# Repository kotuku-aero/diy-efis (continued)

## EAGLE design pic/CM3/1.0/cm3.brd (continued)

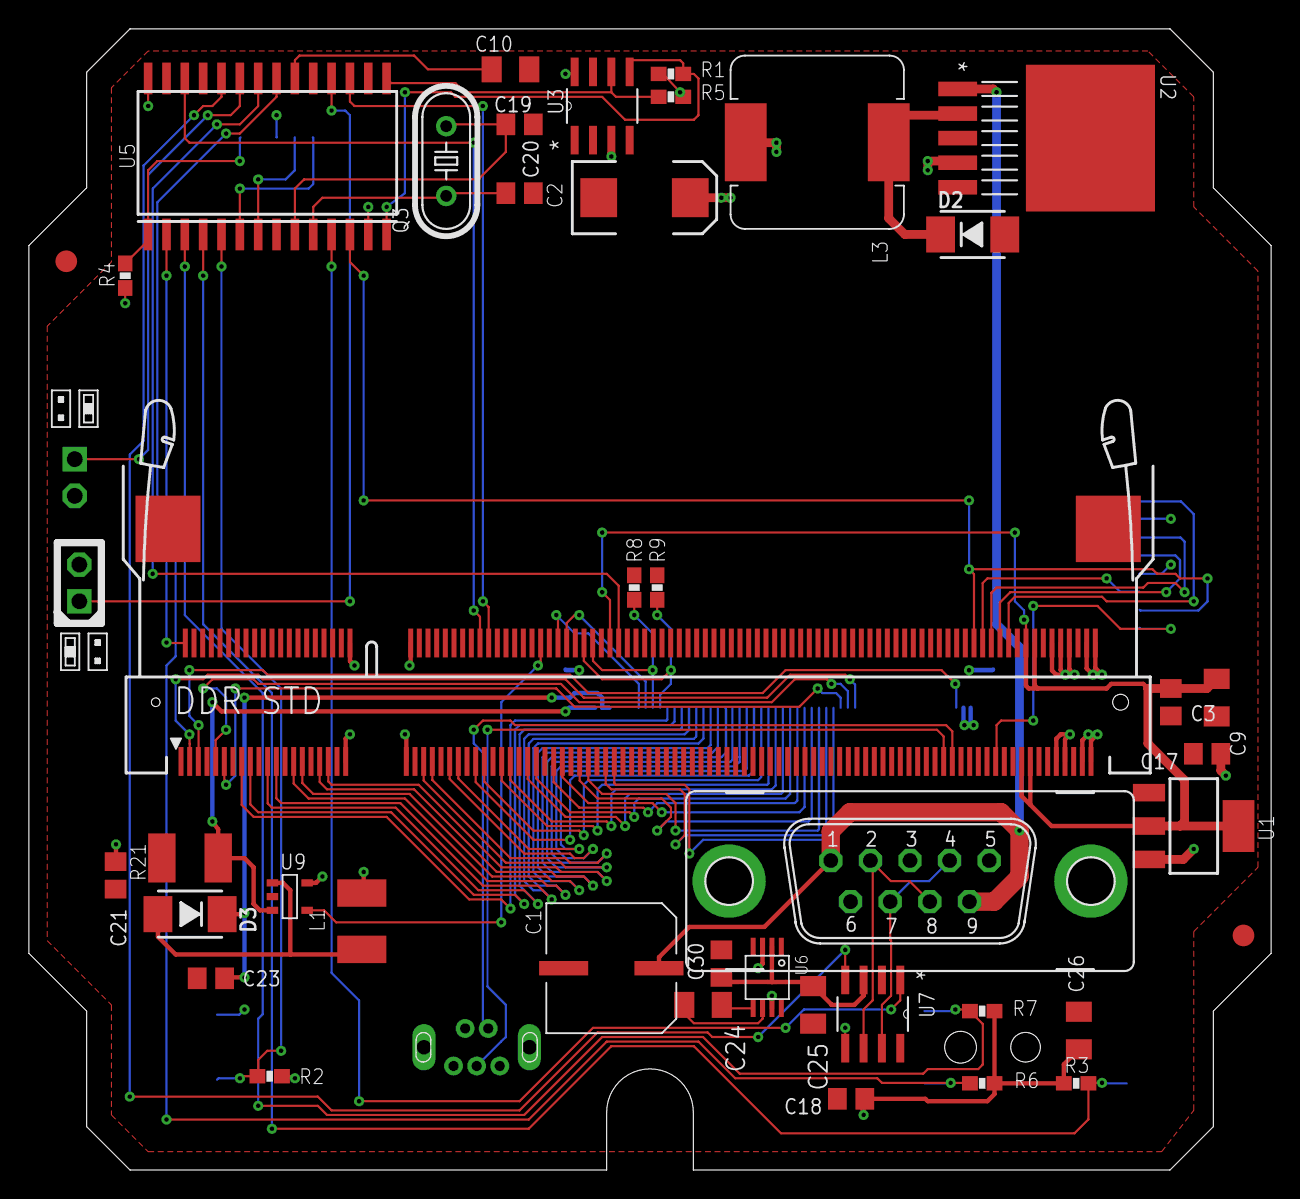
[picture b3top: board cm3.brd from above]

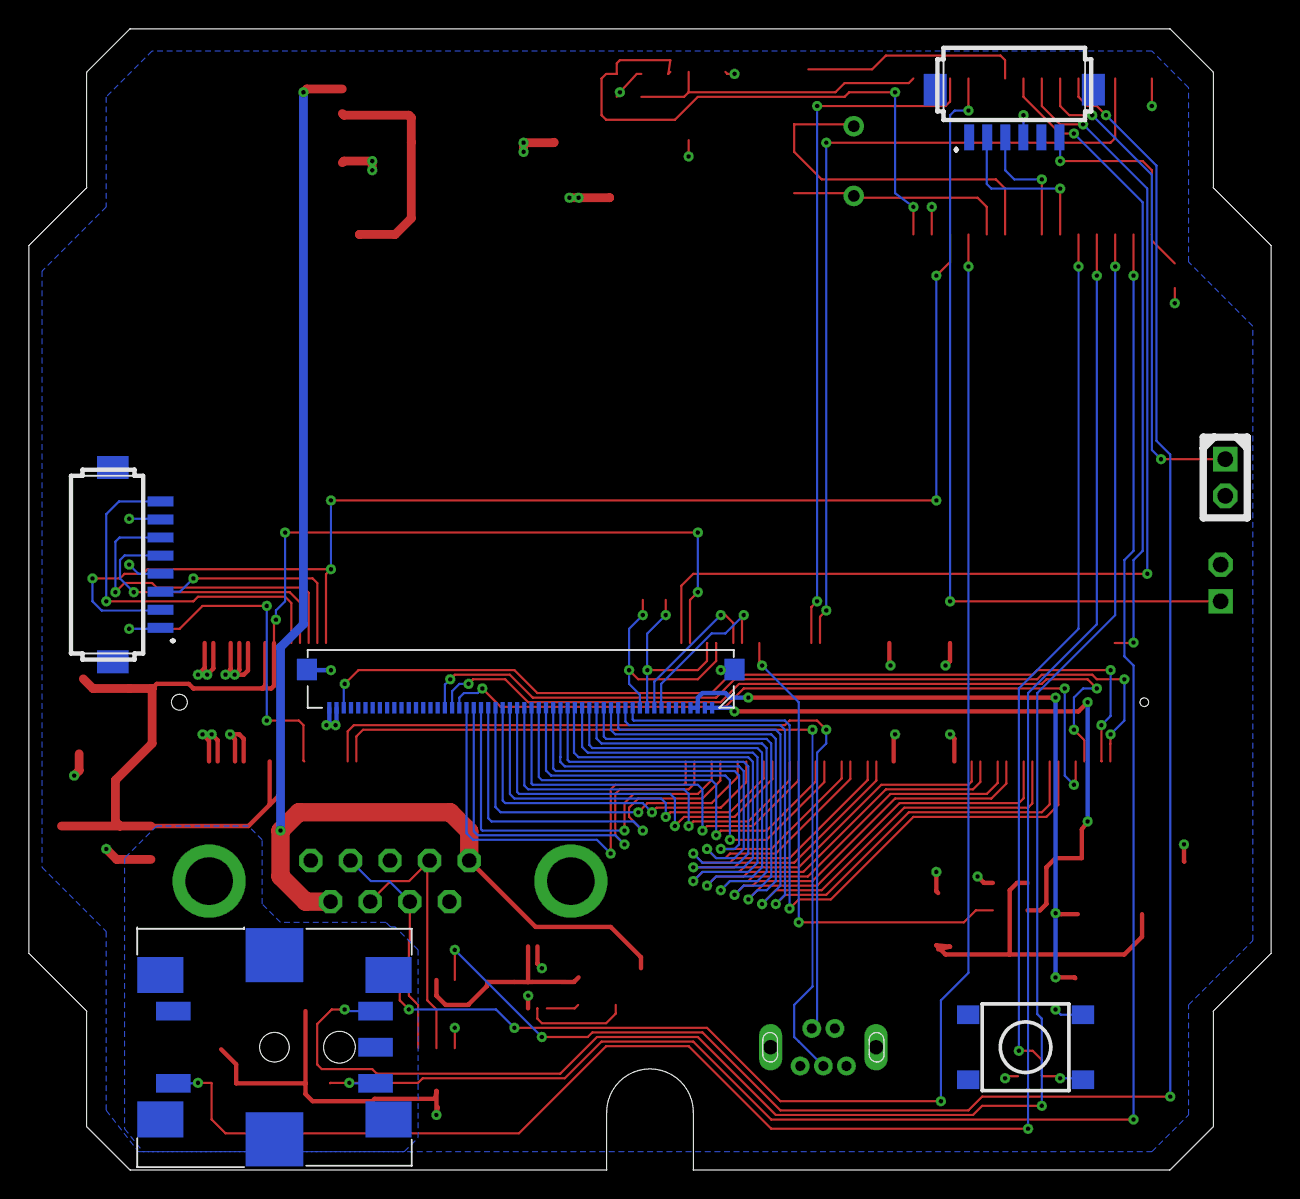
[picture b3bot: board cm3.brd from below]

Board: 2 copper layers, 86.0 x 79.0 mm, 51 parts (7 on the bottom side), 74 nets.

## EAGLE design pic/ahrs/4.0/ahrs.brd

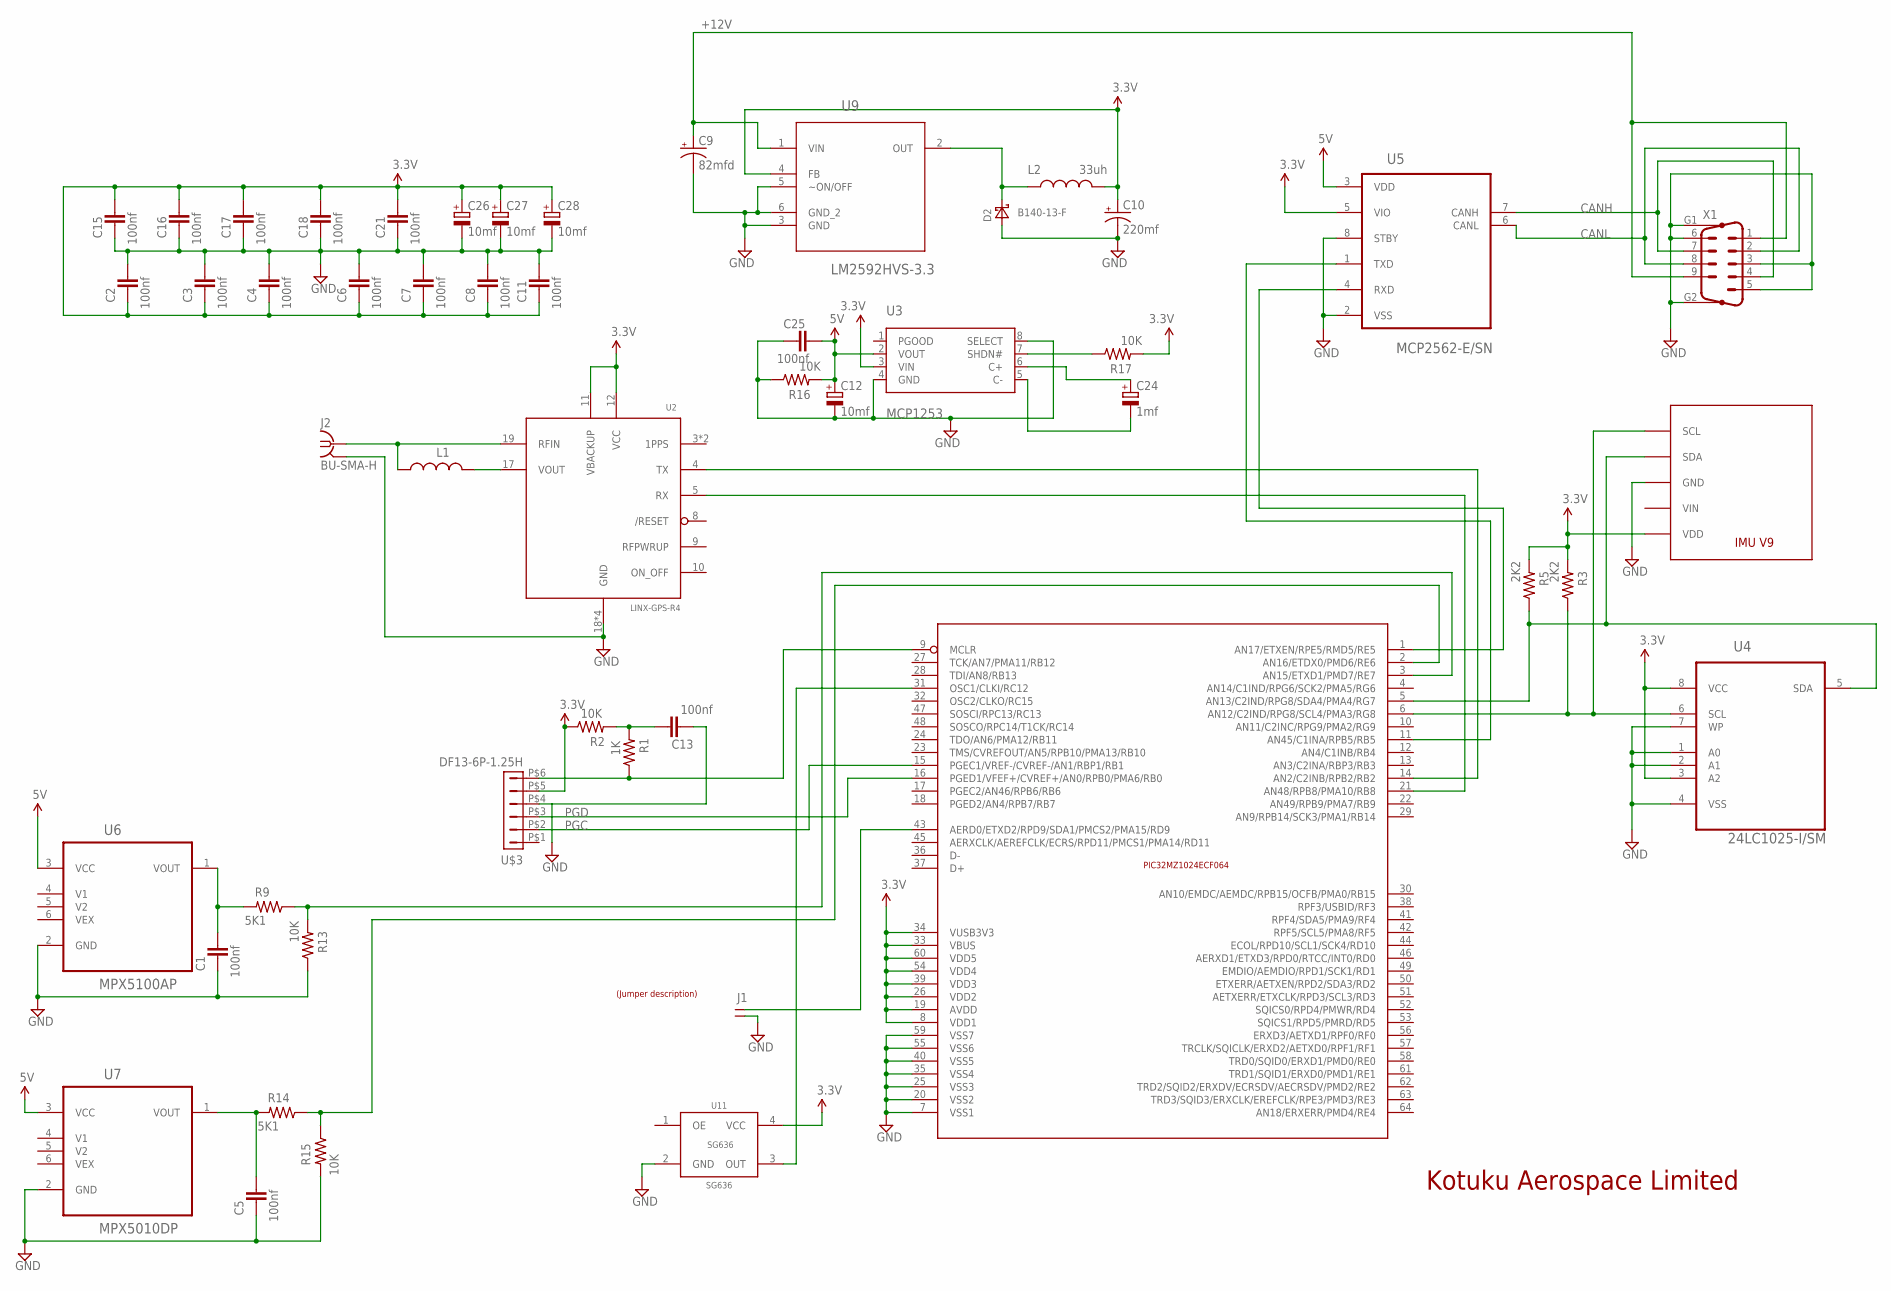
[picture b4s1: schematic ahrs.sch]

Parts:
C1, C2, C3, C4, C5, C6, C7, C8, C11, C13, C15, C16, C17, C18, C21, C25: 100nf; C805
C9: 82mfd; SVPF-E7
C10: 220mf; EIA7343
C12, C26, C27, C28: 10mf; SMC_A
C24: 1mf; SMC_A
D2: B140-13-F; SMA
J1: JUMPER-1X2
J2: BU-SMA-H; PARTNO 5-1814400-1
L1: FERRITE-0603; FB603
L2: 33uh; 1812
R1: 1K; 0603-RES; PARTNO ERJ-3GEYJ103V
R2, R13, R15, R16, R17: 10K; 0603-RES; PARTNO ERJ-3GEYJ103V
R3, R5: 2K2; 0603-RES; PARTNO ERJ-3GEYJ103V
R9, R14: 5K1; 0603-RES; PARTNO ERJ-3GEYJ103V
U2: LINX-GPS-R4; LINX-R4; PARTNO RXM-GPS-R4-T
U3: MCP1253; MSOP8
U4: 24LC1025-I/SM; SOIC8-N_MC
U5: MCP2562-E/SN; SOIC-8N
U6: MPX5100AP; FREESCALE_CASE_867B-04
U7: MPX5010DP; FREESCALE_CASE_867B-04
U8: IMUV9
U9: LM2592HVS-3.3; TO170P1435X457-5N
U11: SG636; PARTNO SG-636PCE 10.000MHZ
U$1: LABEL_JUMPER_1X2; JUMP2_DESC
U$2: PIC32MZ1024; TQFP-64
U$3: DF13-6P-1.25H; DF13A-6P-1.25H
X1: M09HP

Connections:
3.3V: C2.2, C3.2, C4.2, C6.2, C7.2, C8.2, C10.A (+), C11.2, C15.1, C16.1, C17.1, C18.1, C21.1, C26.+, C27.+, C28.+, L2.2, R2.1, R3.2, R5.2, R17.2, U2.11 (VBACKUP), U2.12 (VCC), U3.3 (VIN), U4.3 (A2), U4.8 (VCC), U5.5 (VIO), U8.VDD, U9.4 (FB), U11.4 (VCC), U$2.8 (VDD1), U$2.19 (AVDD), U$2.26 (VDD2), U$2.33 (VBUS), U$2.34 (VUSB3V3), U$2.39 (VDD3), U$2.54 (VDD4), U$2.60 (VDD5), U$3.P$5 (5)
5V: C12.+, C25.1, R16.2, U3.2 (VOUT), U5.3 (VDD), U6.3 (VCC), U7.3 (VCC)
!MCLR: R1.1, U$2.9 (MCLR), U$3.P$6 (6)
+12V: C9.P$2 (+), U9.1 (VIN), X1.1, X1.9
CANH: U5.7 (CANH), X1.4, X1.7
CANL: U5.6 (CANL), X1.2, X1.8
GND: C1.2, C2.1, C3.1, C4.1, C5.2, C6.1, C7.1, C8.1, C9.P$1 (-), C10.C (-), C11.1, C12.-, C13.2, C15.2, C16.2, C17.2, C18.2, C21.2, C25.2, C26.-, C27.-, C28.-, D2.A, J1.2, J2.2, J2.3 (2), J2.4 (2), J2.5 (2), R13.1, R15.2, R16.1, U2.18 (GND), U2.20 (GND), U2.21 (GND), U2.22 (GND), U3.4 (GND), U3.8 (SELECT), U4.1 (A0), U4.2 (A1), U4.4 (VSS), U4.7 (WP), U5.2 (VSS), U5.8 (STBY), U6.2 (GND), U7.2 (GND), U8.GND, U9.3 (GND), U9.5 (~ON/OFF), U9.6 (GND_2), U11.2 (GND), U$2.7 (VSS1), U$2.20 (VSS2), U$2.25 (VSS3), U$2.35 (VSS4), U$2.40 (VSS5), U$2.55 (VSS6), U$2.59 (VSS7), U$3.P$4 (4), X1.3, X1.5, X1.6, X1.G1, X1.G2
unnamed: L1.2, U2.17 (VOUT)
unnamed: J2.1, L1.1, U2.19 (RFIN)
unnamed: U5.4 (RXD), U$2.1 (AN17/ETXEN/RPE5/RMD5/RE5)
unnamed: U11.3 (OUT), U$2.31 (OSC1/CLKI/RC12)
unnamed: C13.1, R1.2, R2.2
unnamed: C1.1, R9.2, U6.1 (VOUT)
unnamed: R9.1, R13.2, U$2.3 (AN15/ETXD1/PMD7/RE7)
unnamed: C5.1, R14.2, U7.1 (VOUT)
unnamed: D2.C, L2.1, U9.2 (OUT)
unnamed: U2.4 (TX), U$2.14 (AN2/C2INB/RPB2/RB2)
unnamed: U2.5 (RX), U$2.21 (AN48/RPB8/PMA10/RB8)
unnamed: J1.1, U$2.43 (AERD0/ETXD2/RPD9/SDA1/PMCS2/PMA15/RD9)
unnamed: U5.1 (TXD), U$2.11 (AN45/C1INA/RPB5/RB5)
unnamed: R17.1, U3.7 (SHDN#)
unnamed: C24.-, U3.5 (C-)
unnamed: C24.+, U3.6 (C+)
PGC: U$2.15 (PGEC1/VREF-/CVREF-/AN1/RBP1/RB1), U$3.P$2 (2)
PGD: U$2.16 (PGED1/VFEF+/CVREF+/AN0/RPB0/PMA6/RB0), U$3.P$3 (3)
PITOT: R14.1, R15.1, U$2.2 (AN16/ETDX0/PMD6/RE6)
SCL: R3.1, U4.6 (SCL), U8.SCL, U$2.6 (AN12/C2IND/RPG8/SCL4/PMA3/RG8)
SDA: R5.1, U4.5 (SDA), U8.SDA, U$2.5 (AN13/C2IND/RPG8/SDA4/PMA4/RG7)
VIN: U8.VIN

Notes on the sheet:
Kotuku Aerospace Limited

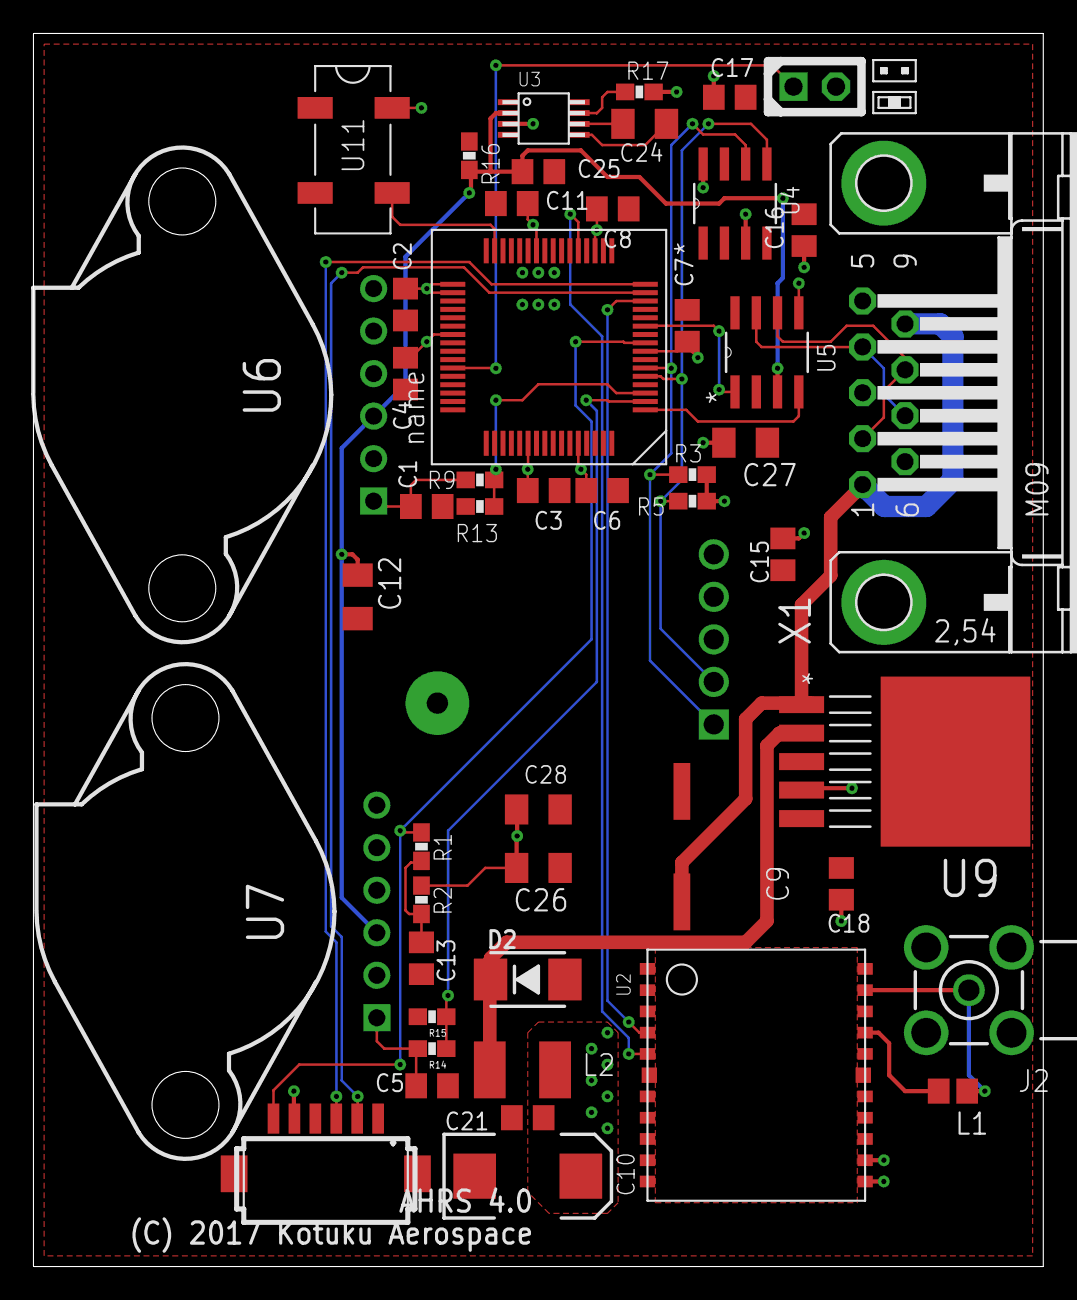
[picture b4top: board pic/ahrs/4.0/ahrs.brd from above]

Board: 2 copper layers, 60.3 x 73.7 mm, 51 parts (0 on the bottom side), 28 nets.

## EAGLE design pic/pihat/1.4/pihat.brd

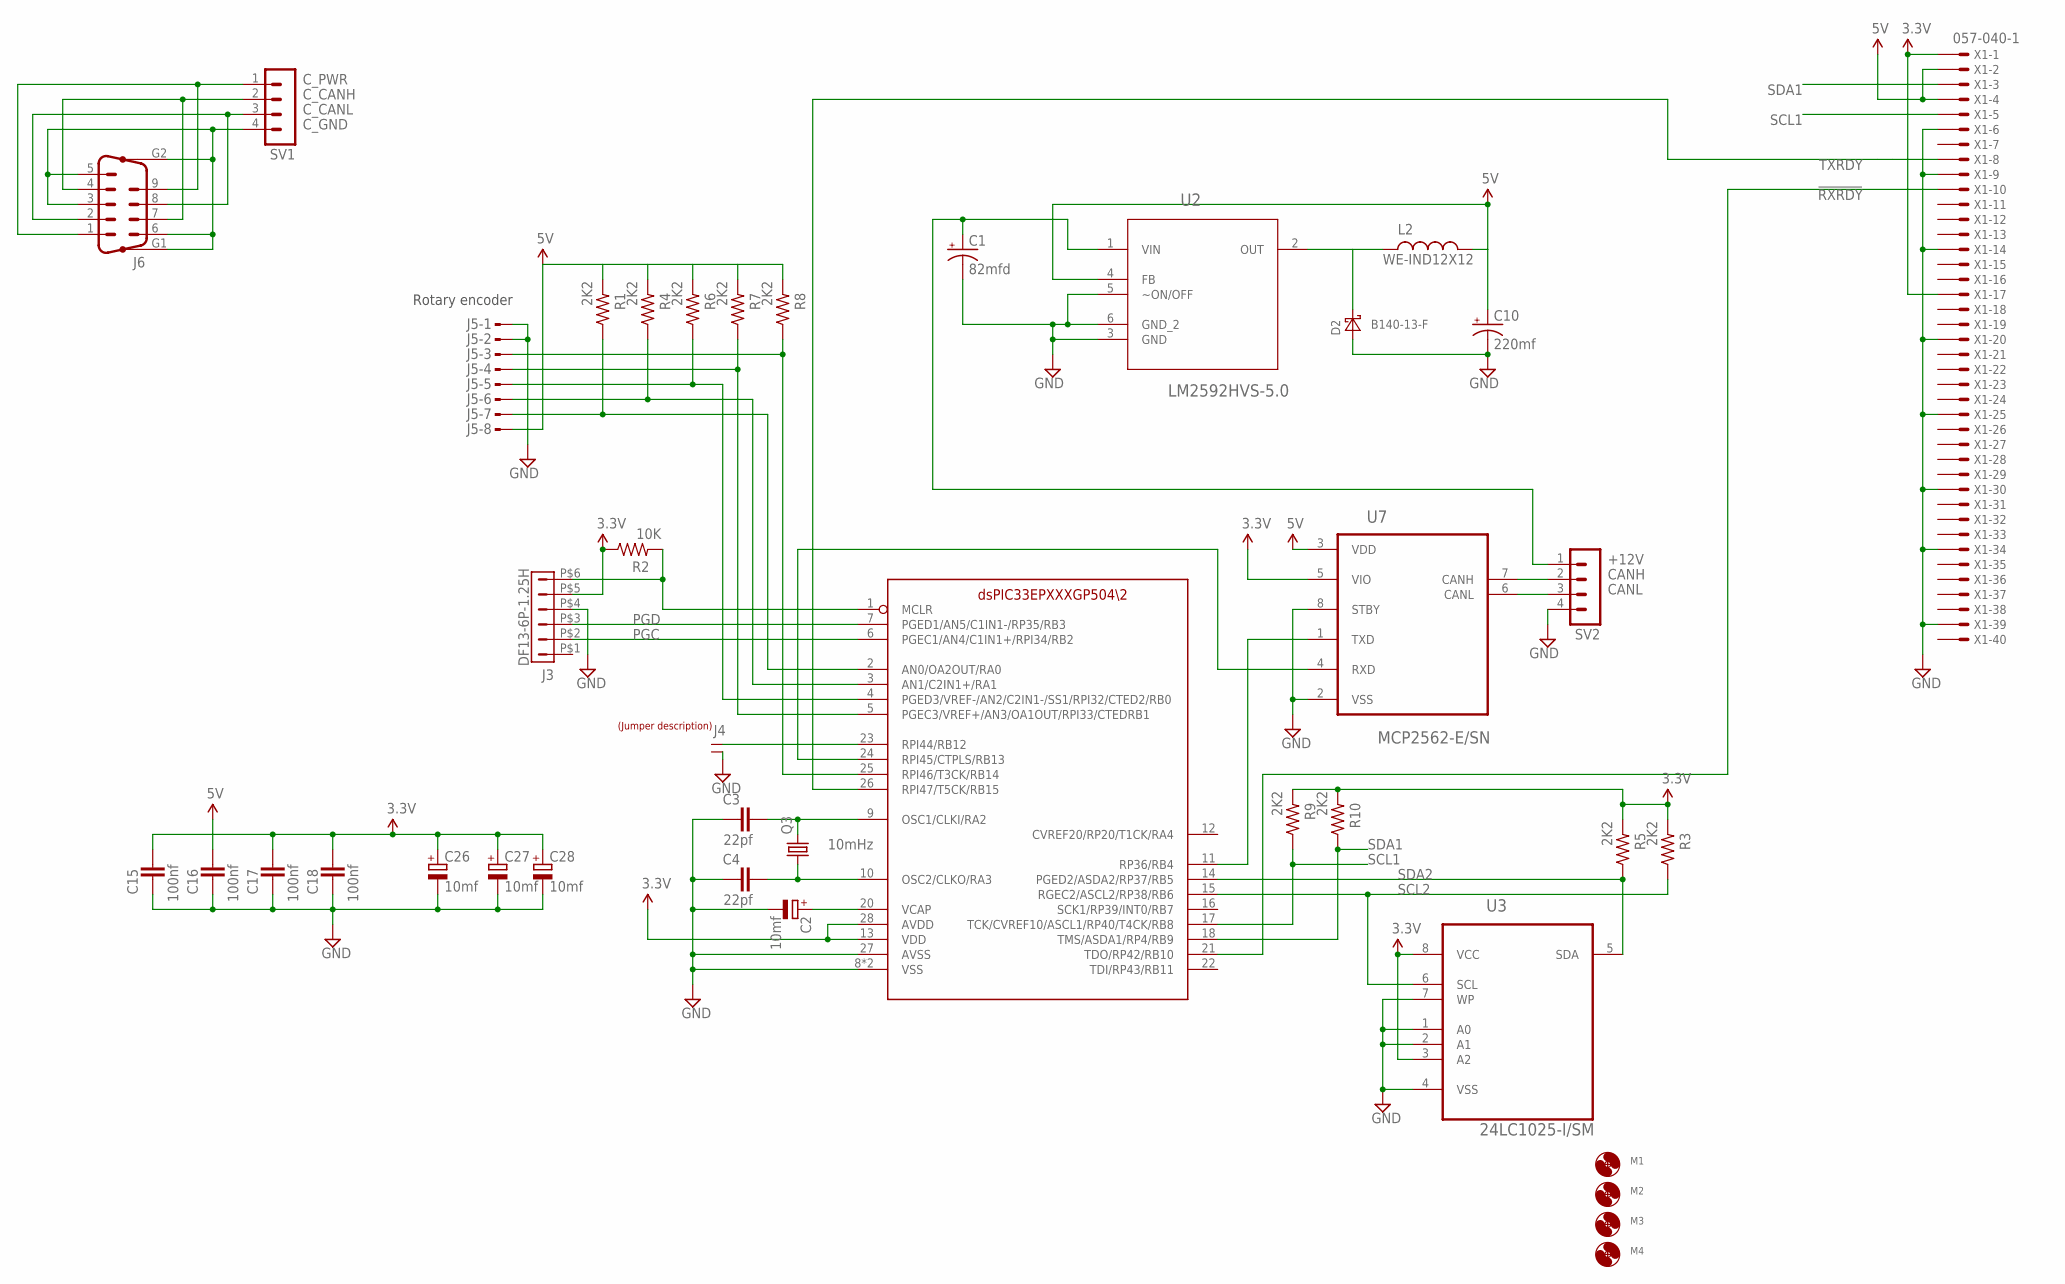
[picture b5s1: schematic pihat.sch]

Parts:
C1: 82mfd; SVPF-E7
C2, C26, C27, C28: 10mf; SMC_A; PARTNO T491A106K004AT
C3, C4: 22pf; C805; PARTNO C0805C220J5GACTU
C10: 220mf; EIA7343; PARTNO T545X227M016ATE035
C15, C16, C17, C18: 100nf; C805; PARTNO CL21F104ZBCNNNC
D2: B140-13-F; SMA; PARTNO B140-13-F
J3: DF13-6P-1.25H; DF13A-6P-1.25H; PARTNO DF13A-6P-1.25H(20)
J4: JUMPER-1X2; PARTNO M20-9770246
J5: MTOP-8; PARTNO 7-215079-8
J6: M09VP
L2: WE-IND12X12; IND12X12
M1, M2, M3, M4: MOUNT-HOLE2.8; 2,8
Q3: 10mHz; HC49/S; PARTNO ATS100B-E
R1, R3, R4, R5, R6, R7, R8, R9, R10: 2K2; 0603-RES; PARTNO RC0603FR-072K2L
R2: 10K; 0603-RES; PARTNO RC0603FR-0710KL
SV1, SV2: MA04-1
U2: LM2592HVS-5.0; TO170P1435X457-5N; PARTNO LM2592HVSX-5.0/NOPB
U3: 24LC1025-I/SM; SOIC8-N_MC; PARTNO 24LC1025T-I/SN
U4: DSPIC33EPXXXGP502; SOIC-28
U7: MCP2562-E/SN; SOIC-8N; PARTNO MCP2562-E/SN
U$1: LABEL_JUMPER_1X2; JUMP2_DESC
X1: 057-040-1

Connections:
3.3V: C15.1, C17.1, C18.1, C26.+, C27.+, C28.+, J3.P$5 (5), R2.1, R3.2, R5.2, R9.2, R10.2, U3.3 (A2), U3.8 (VCC), U4.13 (VDD), U4.28 (AVDD), U7.5 (VIO), X1.1, X1.17
5V: C10.A (+), C16.1, J5.8, L2.P$2 (2), R1.2, R4.2, R6.2, R7.2, R8.2, U2.4 (FB), U7.3 (VDD), X1.2, X1.4
!MCLR: J3.P$6 (6), R2.2, U4.1 (MCLR)
!RXRDY: U4.21 (TDO/RP42/RB10), X1.10
+12V: C1.P$2 (+), SV2.1, U2.1 (VIN)
A+: J5.7, R1.1, U4.2 (AN0/OA2OUT/RA0)
A-: J5.6, R4.1, U4.3 (AN1/C2IN1+/RA1)
B+: J5.5, R6.1, U4.4 (PGED3/VREF-/AN2/C2IN1-/SS1/RPI32/CTED2/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)
B-: J5.4, R7.1, U4.5 (PGEC3/VREF+/AN3/OA1OUT/RPI33/CTEDRB1)
CANH: SV2.2, U7.7 (CANH)
CANL: SV2.3, U7.6 (CANL)
C_CANH: J6.4, J6.7, SV1.2
C_CANL: J6.2, J6.8, SV1.3
C_GND: J6.3, J6.5, J6.6, J6.G1, J6.G2, SV1.4
C_PWR: J6.1, J6.9, SV1.1
GND: C1.P$1 (-), C2.-, C3.2, C4.2, C10.C (-), C15.2, C16.2, C17.2, C18.2, C26.-, C27.-, C28.-, D2.A, J3.P$4 (4), J4.2, J5.1, J5.2, SV2.4, U2.3 (GND), U2.5 (~ON/OFF), U2.6 (GND_2), U3.1 (A0), U3.2 (A1), U3.4 (VSS), U3.7 (WP), U4.8 (VSS), U4.19 (VSS), U4.27 (AVSS), U7.2 (VSS), U7.8 (STBY), X1.6, X1.9, X1.14, X1.20, X1.25, X1.30, X1.34, X1.39
unnamed: D2.C, L2.P$1 (1), U2.2 (OUT)
unnamed: C3.1, Q3.2, U4.9 (OSC1/CLKI/RA2)
unnamed: U4.24 (RPI45/CTPLS/RB13), U7.4 (RXD)
unnamed: C2.+, U4.20 (VCAP)
unnamed: U4.11 (RP36/RB4), U7.1 (TXD)
unnamed: C4.1, Q3.1, U4.10 (OSC2/CLKO/RA3)
PGC: J3.P$2 (2), U4.6 (PGEC1/AN4/C1IN1+/RPI34/RB2)
PGD: J3.P$3 (3), U4.7 (PGED1/AN5/C1IN1-/RP35/RB3)
RESET#: J4.1, U4.23 (RPI44/RB12)
SCL1: R9.1, U4.17 (TCK/CVREF10/ASCL1/RP40/T4CK/RB8), X1.5
SCL2: R3.1, U3.6 (SCL), U4.15 (RGEC2/ASCL2/RP38/RB6)
SDA1: R10.1, U4.18 (TMS/ASDA1/RP4/RB9), X1.3
SDA2: R5.1, U3.5 (SDA), U4.14 (PGED2/ASDA2/RP37/RB5)
SW1: J5.3, R8.1, U4.25 (RPI46/T3CK/RB14)
TXRDY: U4.26 (RPI47/T5CK/RB15), X1.8

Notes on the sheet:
Rotary encoder

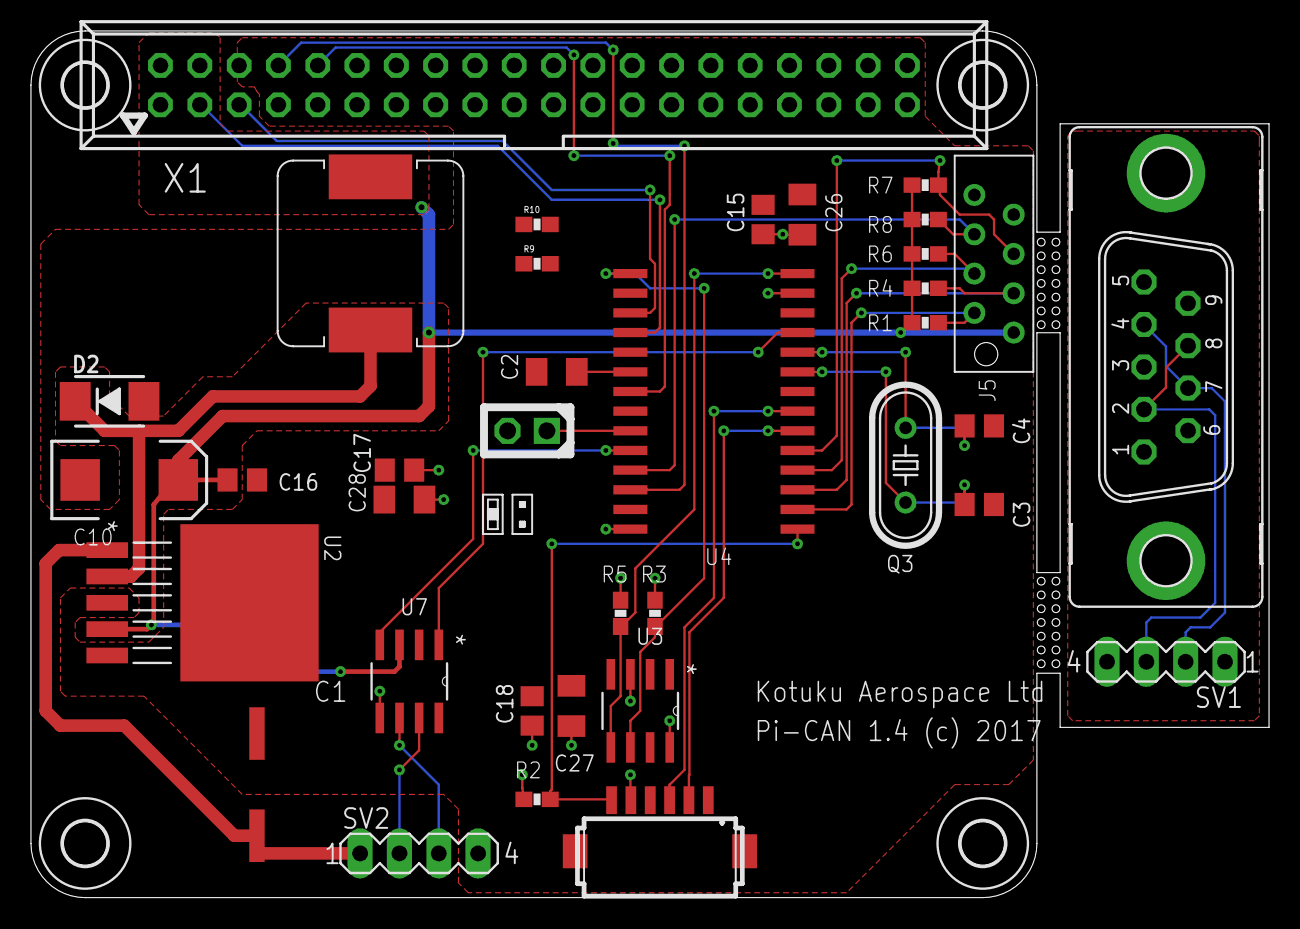
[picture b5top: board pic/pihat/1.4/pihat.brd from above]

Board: 2 copper layers, 80.0 x 56.0 mm, 41 parts (0 on the bottom side), 31 nets.

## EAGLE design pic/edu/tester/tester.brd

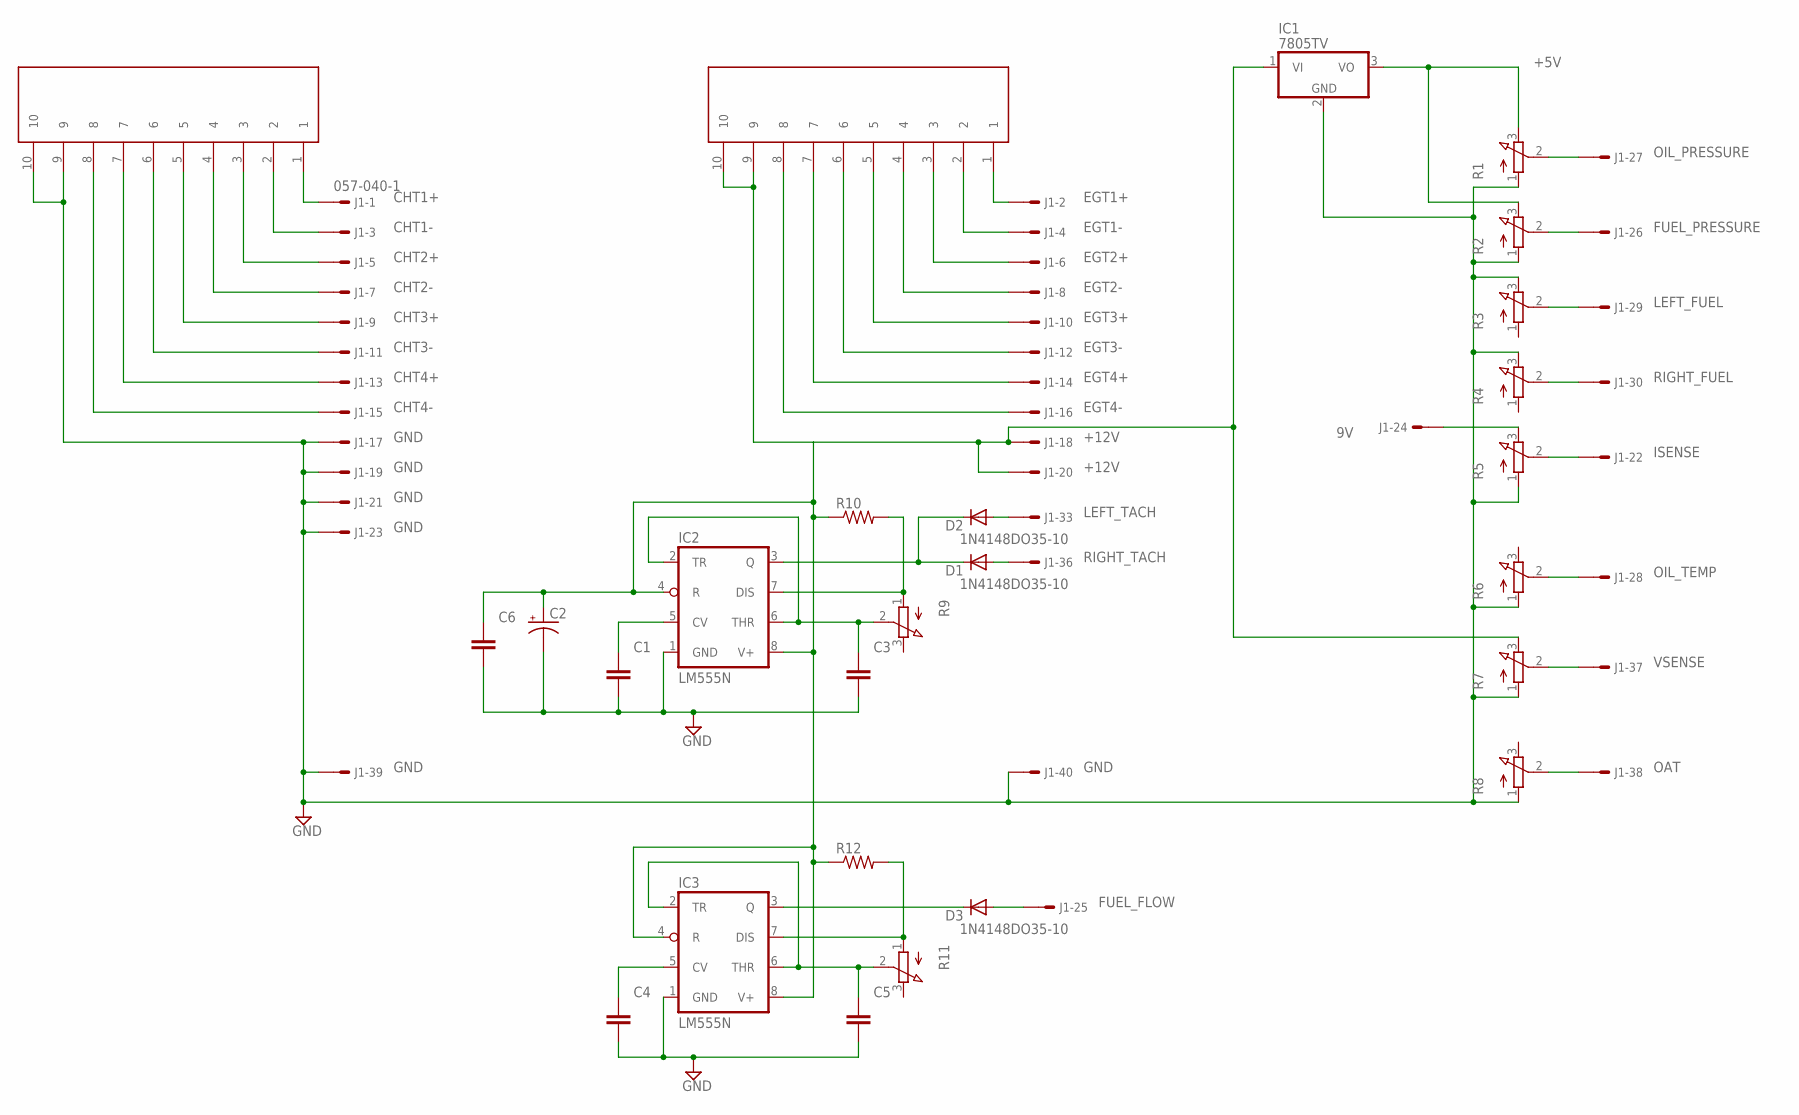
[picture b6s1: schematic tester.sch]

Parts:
C1, C3, C4, C5, C6: CAPACITOR_NPOL-PTH_0.1"; C0.1PTH
C2: CAP_POLPTH2; CPOL-RADIAL-10UF-25V
D1, D2, D3: 1N4148DO35-10; DO35-10
IC1: 7805TV; TO220V
IC2, IC3: LM555N; DIL08
J1: 057-040-1; PARTNO SBH11-PBPC-D20-ST-BK
R1, R2, R3, R4, R5, R6, R7, R8, R9, R11: 3RP/1610N
R10, R12: RESISTORPTH-1/4W; AXIAL-0.4
TB2, TB4: 282847-10; PARTNO 1-282847-0

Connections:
9V: J1.24, R5.3 (E)
+5V: IC1.3 (VO), R1.3 (E), R2.3 (E)
+12V: C2.1 (+), C6.1, IC1.1 (VI), IC2.4 (R), IC2.8 (V+), IC3.4 (R), IC3.8 (V+), J1.18, J1.20, R7.3 (E), R10.P$1 (1), R12.P$1 (1), TB4.9, TB4.10
CHT1+: J1.1, TB2.1
CHT1-: J1.3, TB2.2
CHT2+: J1.5, TB2.3
CHT2-: J1.7, TB2.4
CHT3+: J1.9, TB2.5
CHT3-: J1.11, TB2.6
CHT4+: J1.13, TB2.7
CHT4-: J1.15, TB2.8
EGT1+: J1.2, TB4.1
EGT1-: J1.4, TB4.2
EGT2+: J1.6, TB4.3
EGT2-: J1.8, TB4.4
EGT3+: J1.10, TB4.5
EGT3-: J1.12, TB4.6
EGT4+: J1.14, TB4.7
EGT4-: J1.16, TB4.8
FF: C5.1, IC3.2 (TR), IC3.6 (THR), R11.2 (S)
FUEL_FLOW: D3.A, J1.25
FUEL_PRESSURE: J1.26, R2.2 (S)
GND: C1.2, C2.2 (-), C3.2, C4.2, C5.2, C6.2, IC1.2 (GND), IC2.1 (GND), IC3.1 (GND), J1.17, J1.19, J1.21, J1.23, J1.39, J1.40, R1.1 (A), R2.1 (A), R3.3 (E), R4.3 (E), R5.1 (A), R6.1 (A), R7.1 (A), R8.1 (A), TB2.9, TB2.10
ISENSE: J1.22, R5.2 (S)
LEFT_FUEL: J1.29, R3.2 (S)
LEFT_TACH: D2.A, J1.33
unnamed: C1.1, IC2.5 (CV)
unnamed: IC2.7 (DIS), R9.1 (A), R10.P$2 (2)
unnamed: D1.C, D2.C, IC2.3 (Q)
unnamed: C4.1, IC3.5 (CV)
unnamed: IC3.7 (DIS), R11.1 (A), R12.P$2 (2)
unnamed: D3.C, IC3.3 (Q)
OAT: J1.38, R8.2 (S)
OIL_PRESSURE: J1.27, R1.2 (S)
OIL_TEMP: J1.28, R6.2 (S)
RIGHT_FUEL: J1.30, R4.2 (S)
RIGHT_TACH: D1.A, J1.36
RPM: C3.1, IC2.2 (TR), IC2.6 (THR), R9.2 (S)
VSENSE: J1.37, R7.2 (S)

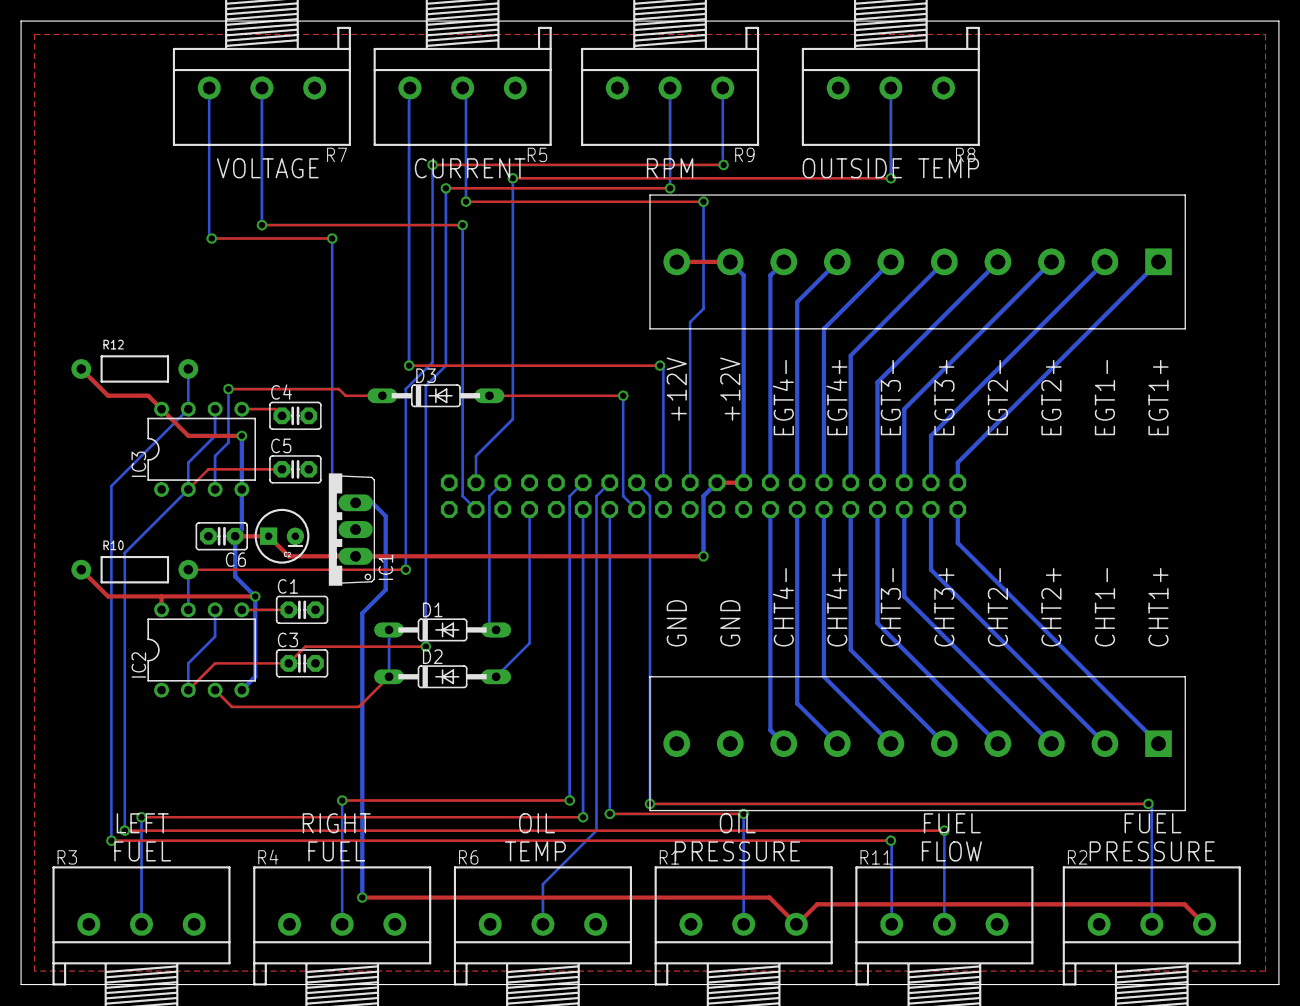
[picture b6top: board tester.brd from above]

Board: 2 copper layers, 119.4 x 91.4 mm, 27 parts (1 on the bottom side), 39 nets.
